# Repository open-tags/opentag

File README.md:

# opentag · early UWB prototype

Hardware, firmware, and an iOS app from the early opentags research project.

> **Historical R&D reference.** This prototype predates opentag U1 and uses different hardware and firmware. For current products and setup guides, visit [opentags](https://open-tags.com/) and the [documentation](https://open-tags.com/docs/).

[Hardware](Hardware/) · [Firmware](Firmware/README.md) · [iOS app](iOS/OpenTags/README.md) · [Current ROS 2 source](https://github.com/open-tags/open-tags.github.io/tree/main/ros2)

<p align="center">
  
  <br>
  <sub>Historical prototype PCB · rendered directly from the KiCad board and its assigned 3D models</sub>
</p>

Some components have no assigned 3D model and appear as bare footprints. [Render details](assets/README.md)

<p align="center">
  
  <br>
  <sub>Original prototype · exploded CAD view</sub>
</p>

## Explore the prototype

The project explored ultra-wideband (UWB) ranging and iPhone interaction. These files preserve that development work; they are not a complete, validated product release.

| Resource | What is included | Start here |
| --- | --- | --- |
| Hardware | KiCad schematics and board layouts, component libraries, BOMs, and fabrication exports | [KiCad project](Hardware/Hardware.kicad_pro) |
| Firmware | Arduino / PlatformIO experiments and bundled radio libraries | [Build notes and missing dependencies](Firmware/README.md) |
| iOS | Xcode project based on Apple's Nearby Interaction accessory sample | [iOS setup notes](iOS/OpenTags/README.md) |

## Before building

- **Firmware dependencies are incomplete.** The active PlatformIO target is `xiaoble_adafruit_nrf52`. The source includes `niq.h` and the configuration references NIQ libraries that are not included in this repository. A clean checkout is not ready to build; see the [firmware notes](Firmware/README.md).
- **The iOS app is experimental.** Its setup notes require an iPhone with Apple's U1 chip and a compatible accessory. Apple's U1 chip is unrelated to the opentag U1 product name.
- **Hardware files record prototype revisions.** Check the schematic, board revision, and firmware pin assignments together before fabrication or flashing.

## Current opentags resources

opentags now builds tracking hardware and integration tools for robotics. Start with the [website](https://open-tags.com/) for current products, the [documentation](https://open-tags.com/docs/) for setup, or the [ROS 2 source](https://github.com/open-tags/open-tags.github.io/tree/main/ros2) for robot integration.

This repository's prototype files and license do not describe the hardware, firmware, or licensing of current products.

## Questions and corrections

Use [Issues](https://github.com/open-tags/opentag/issues) for questions or corrections about this prototype. Include the board revision, toolchain, and relevant logs when reporting a build problem. For current product inquiries, contact [hello@open-tags.com](mailto:hello@open-tags.com).

## License

See the repository's [MIT license](LICENSE). Bundled third-party components retain their own license notices, including the [iOS sample](iOS/OpenTags/LICENSE/LICENSE.txt) and [Adafruit nRFCrypto](Firmware/lib/Adafruit_nRFCrypto/LICENSE).

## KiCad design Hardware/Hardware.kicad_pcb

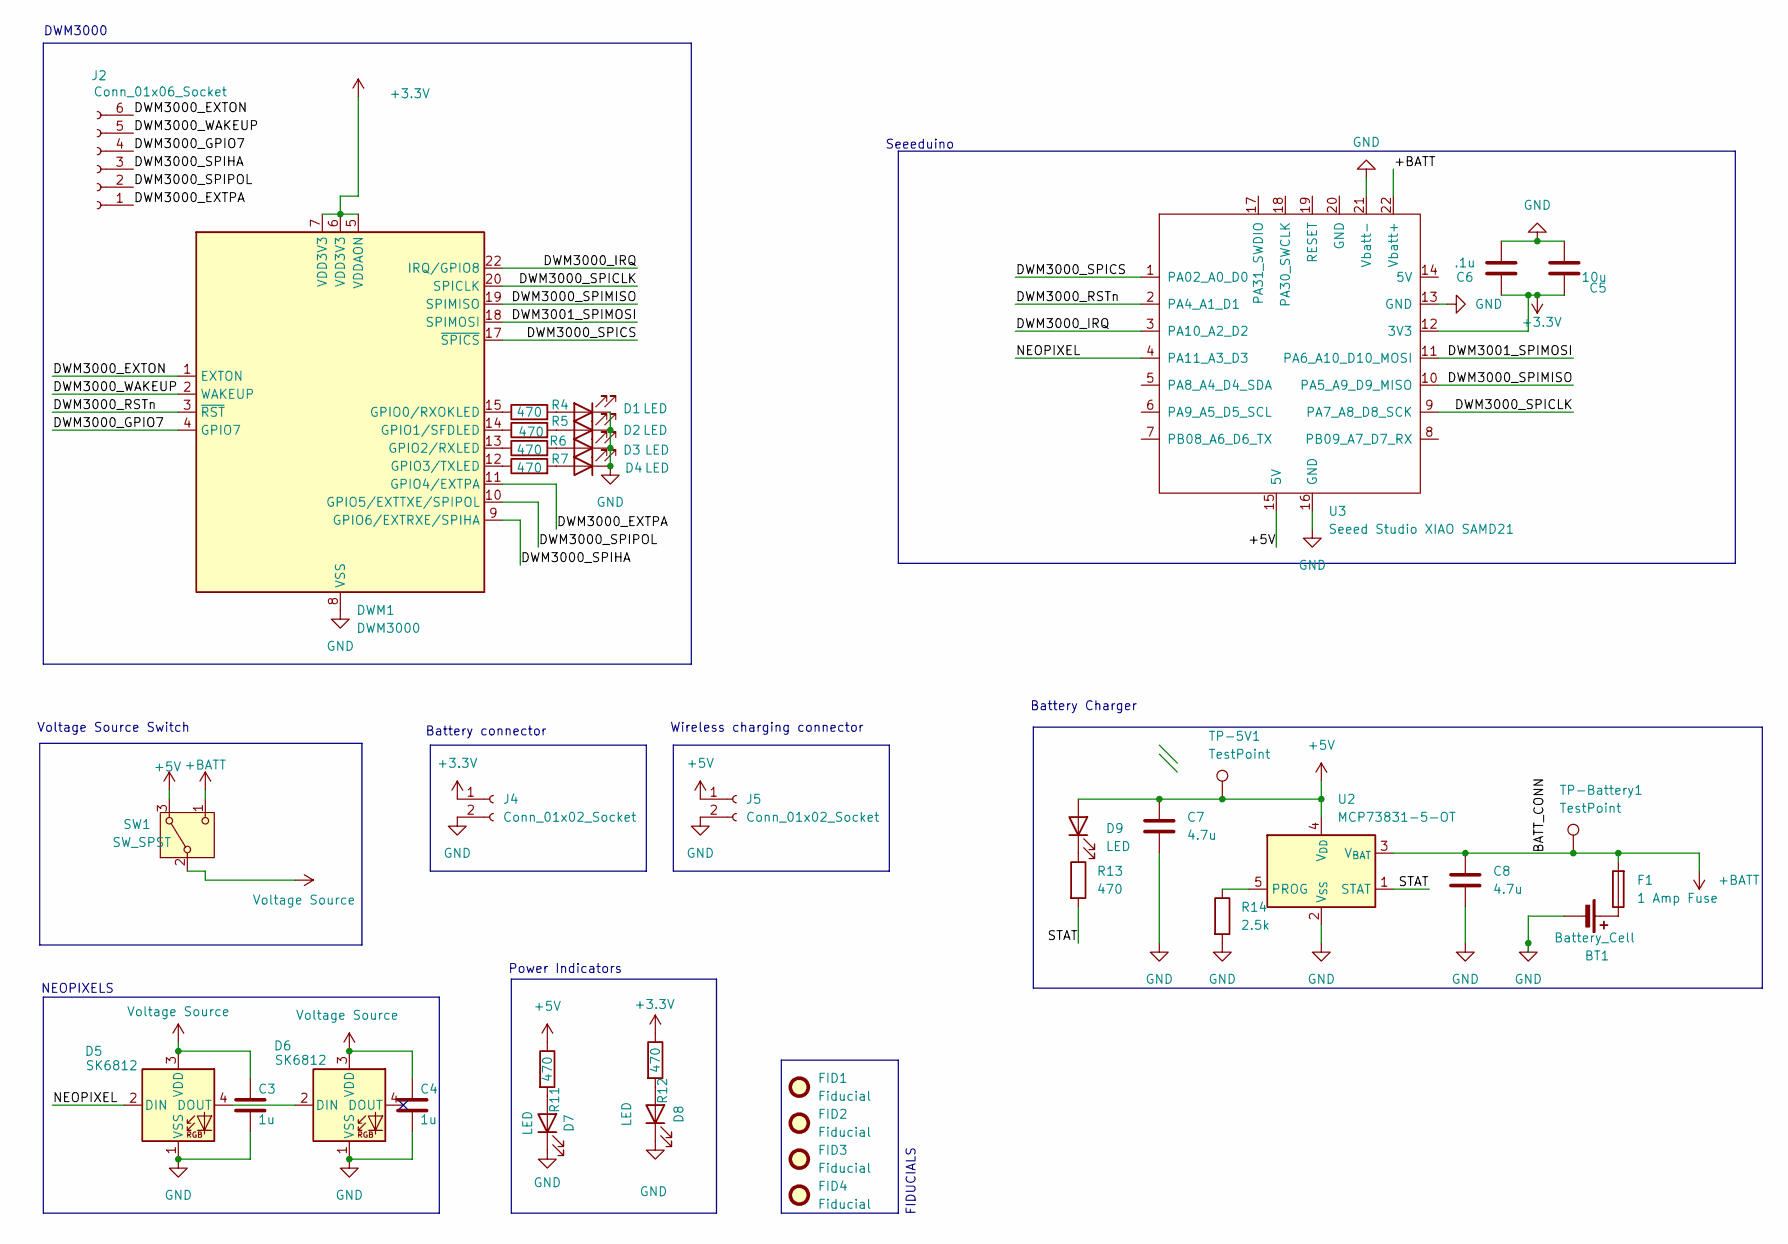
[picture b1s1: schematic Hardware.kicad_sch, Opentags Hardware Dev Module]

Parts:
BT1: Battery_Cell; PinHeader_1x02_P2.54mm_Vertical
C3, C4: 1u; C_0603_1608Metric
C5: 10u; C_0603_1608Metric
C6: .1u; C_0603_1608Metric
C7, C8: 4.7u; C_0603_1608Metric
D1, D2, D3, D4, D7, D8: LED; LED_0603_1608Metric
D5, D6: SK6812; LED_SK6812_PLCC4_5.0x5.0mm_P3.2mm
D9: LED; R_0603_1608Metric
DWM1: DWM3000; DWM1000
F1: 1 Amp Fuse; Fuse_0603_1608Metric
FID1, FID2, FID3, FID4: Fiducial; Fiducial_1mm_Mask2mm
J2: Conn_01x06_Socket; PinHeader_1x06_P2.00mm_Vertical
J4, J5: Conn_01x02_Socket; PinHeader_1x02_P2.54mm_Vertical
R4, R5, R6, R7, R11, R12, R13: 470; R_0603_1608Metric
R14: 2.5k; R_0603_1608Metric
SW1: SW_SPST; SW_JS102011SAQN
TP-5V1: TestPoint; TestPoint_Pad_D2.0mm
TP-Battery1: TestPoint; TestPoint_Pad_D2.0mm
U2: MCP73831-5-OT; SOT-23-5
U3: Seeed Studio XIAO SAMD21; XIAO-nRF52840-Sense-14P-2.54-21X17.8MM

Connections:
+3.3V: C5.1, C6.1, DWM1.5 (VDDAON), DWM1.6 (VDD3V3), DWM1.7 (VDD3V3), J4.1, R12.1, U3.12 (3V3)
+5V: C7.1, D9.2 (A), J5.1, R11.1, SW1.3 (A), TP-5V1.1, U2.4 (V_{DD}), U3.15 (5V)
+BATT: C8.1, F1.2, SW1.1 (C), TP-Battery1.1, U2.3 (V_{BAT}), U3.22 (Vbatt+)
/DWM3000_EXTON: DWM1.1 (EXTON), J2.6
/DWM3000_EXTPA: DWM1.11 (GPIO4/EXTPA), J2.1
/DWM3000_GPIO7: DWM1.4 (GPIO7), J2.4
/DWM3000_IRQ: DWM1.22 (IRQ/GPIO8), U3.3 (PA10_A2_D2)
/DWM3000_RSTn: DWM1.3 (~RST), U3.2 (PA4_A1_D1)
/DWM3000_SPICLK: DWM1.20 (SPICLK), U3.9 (PA7_A8_D8_SCK)
/DWM3000_SPICS: DWM1.17 (~SPICS), U3.1 (PA02_A0_D0)
/DWM3000_SPIHA: DWM1.9 (GPIO6/EXTRXE/SPIHA), J2.3
/DWM3000_SPIMISO: DWM1.19 (SPIMISO), U3.10 (PA5_A9_D9_MISO)
/DWM3000_SPIPOL: DWM1.10 (GPIO5/EXTTXE/SPIPOL), J2.2
/DWM3000_WAKEUP: DWM1.2 (WAKEUP), J2.5
/DWM3001_SPIMOSI: DWM1.18 (SPIMOSI), U3.11 (PA6_A10_D10_MOSI)
/NEOPIXEL: D5.2 (DIN), U3.4 (PA11_A3_D3)
/STAT: R13.2, U2.1 (STAT)
GND: BT1.2 (-), C3.1, C4.1, C5.2, C6.2, C7.2, C8.2, D1.1 (K), D2.1 (K), D3.1 (K), D4.1 (K), D5.1 (VSS), D6.1 (VSS), D7.1 (K), D8.1 (K), DWM1.8 (VSS), DWM1.16 (VSS), DWM1.21 (VSS), DWM1.23 (VSS), DWM1.24 (VSS), J4.2, J5.2, R14.2, U2.2 (V_{SS}), U3.13 (GND), U3.16 (GND), U3.21 (Vbatt-)
unnamed: BT1.1 (+), F1.1
unnamed: D1.2 (A), R4.2
unnamed: D2.2 (A), R5.2
unnamed: D3.2 (A), R6.2
unnamed: D4.2 (A), R7.2
unnamed: D5.4 (DOUT), D6.2 (DIN)
unnamed: D7.2 (A), R11.2
unnamed: D8.2 (A), R12.2
unnamed: D9.1 (K), R13.1
unnamed: DWM1.15 (GPIO0/RXOKLED), R4.1
unnamed: DWM1.14 (GPIO1/SFDLED), R5.1
unnamed: DWM1.13 (GPIO2/RXLED), R6.1
unnamed: DWM1.12 (GPIO3/TXLED), R7.1
unnamed: R14.1, U2.5 (PROG)
Voltage Source: C3.2, C4.2, D5.3 (VDD), D6.3 (VDD), SW1.2 (B)

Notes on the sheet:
Seeeduino
DWM3000
FIDUCIALS
Wireless charging connector
Battery Charger
NEOPIXELS
Power Indicators
Battery connector
Voltage Source Switch

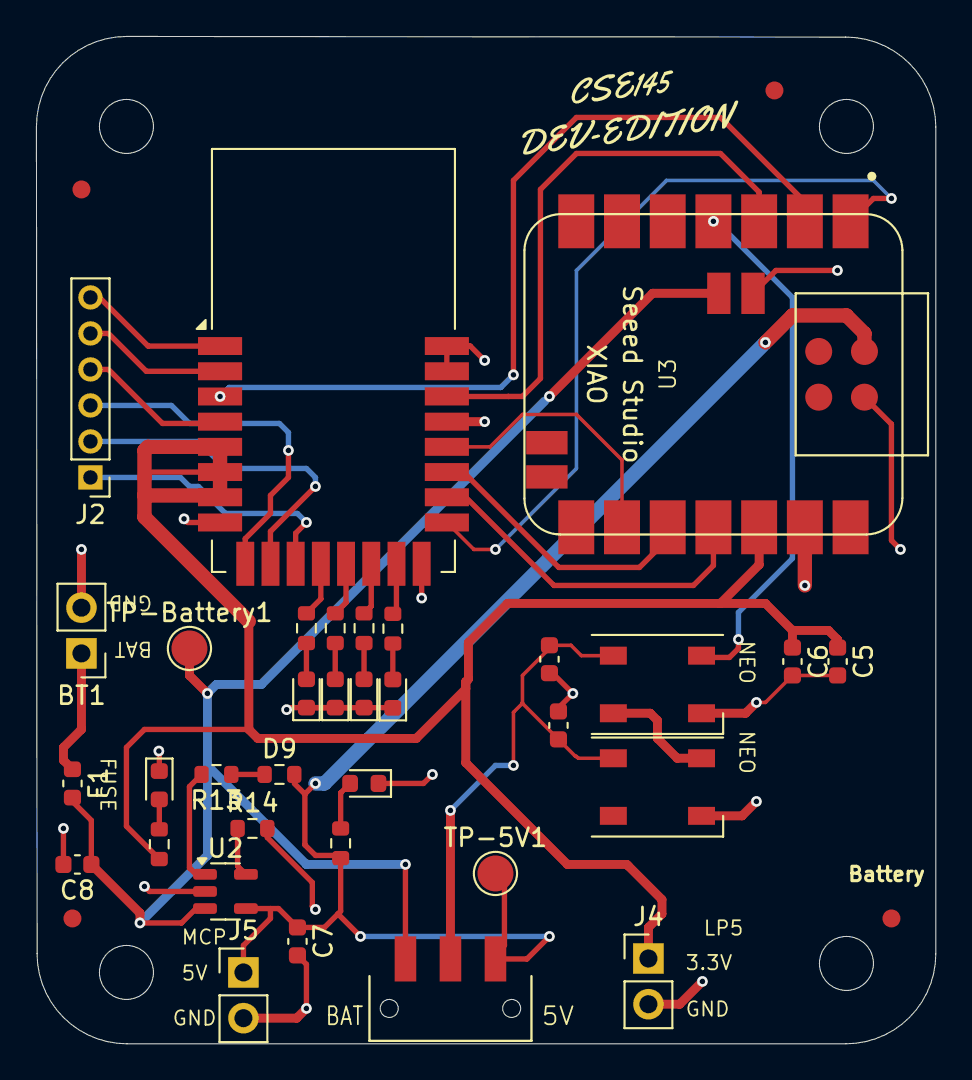
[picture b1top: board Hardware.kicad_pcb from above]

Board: 2 copper layers, 50.0 x 56.0 mm, 38 parts (0 on the bottom side), 33 nets.

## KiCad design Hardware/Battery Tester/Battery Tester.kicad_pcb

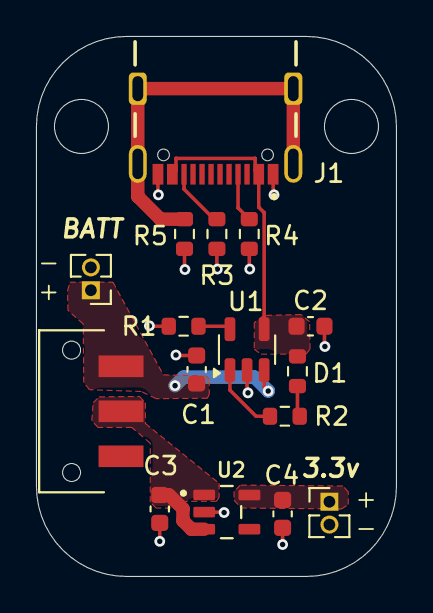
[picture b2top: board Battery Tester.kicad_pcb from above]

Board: 2 copper layers, 20.0 x 30.0 mm, 16 parts (0 on the bottom side), 11 nets.

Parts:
3.3v: Conn_01x02_Socket; PinHeader_1x02_P1.27mm_Vertical
BATT: Battery_Cell; PinHeader_1x02_P1.27mm_Vertical
C1, C2: 4.7u; C_0603_1608Metric
C3, C4: 1u; C_0603_1608Metric
D1: LED; R_0603_1608Metric
J1: USB4105-GF-A; GCT_USB4105-GF-A
R1: 2k; R_0603_1608Metric
R2: 470; R_0603_1608Metric
R3, R4: 5k1; R_0603_1608Metric
R5: 100k; R_0603_1608Metric
SW1: SW_SPST; SW_JS102011SAQN
U1: MCP73831-5-OT; SOT-23-5
U2: LP5907MFX-3.3_NOPB; SOT95P280X145-5N

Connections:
+3.3V: 3.3v.1, C4.1, U2.5 (OUT)
+5V: C2.1, D1.2 (A), J1.A4_B9 (VBUS), J1.B4_A9 (VBUS), U1.4 (V_{DD})
+BATT: C3.1, SW1.2 (B), U2.1 (IN), U2.3 (EN)
/BATT_CONN: BATT.1 (+), C1.1, SW1.1 (A), U1.3 (V_{BAT})
/STAT: R2.2, U1.1 (STAT)
GND: 3.3v.2, BATT.2 (-), C1.2, C2.2, C3.2, C4.2, J1.A1_B12 (GND), J1.B1_A12 (GND), R1.2, R3.2, R4.2, R5.2, U1.2 (V_{SS}), U2.2 (GND)
unnamed: D1.1 (K), R2.1
unnamed: J1.A5 (CC1), R4.1
unnamed: J1.B5 (CC2), R3.1
unnamed: J1.SH1 (SHELL_GND), J1.SH2 (SHELL_GND), J1.SH3 (SHELL_GND), J1.SH4 (SHELL_GND), R5.1
unnamed: R1.1, U1.5 (PROG)

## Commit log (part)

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2024-03-19 Firmware init
2024-04-07 Init
2024-04-10 battery tester board
2024-04-16 Adding PDFs for the schematics
2024-04-25 Initialize swift proj
2024-04-25 Add def proj
2024-04-25 Remove nearby interaction demo
2024-04-25 Remove OpenTags subfolder (.git issue)
2024-04-25 Add default proj w/o git
2024-04-29 firmware Initialization and DWM3000 API setup (makerfabs)
2024-04-30 Fixed README and added newline character to DEV ID FAILED line
2024-04-30 Initial commit of new feature/battery
2024-04-30 readme too
2024-05-12 Added BLE notification capabilites
2024-05-21 Switched to nrF
2024-05-22 Uploading nRF code, all immediate dependencies seem to be fine; just need to remove RTOS
2024-05-22 Added more dependencies to platformio.ini
2024-05-23 Added more I-
2024-05-29 Done with middleware
2024-05-31 tried implementing TWR
2024-05-31 Added a comment
2024-06-04 Added stuff
2024-06-04 hardware updates
2024-06-04 Clean up Part 1
2024-06-04 Clean up
2024-06-05 New proj
2024-06-05 Copy of NINearbyAccessory
2024-06-06 Add AR assistance, commented out - crash on build
